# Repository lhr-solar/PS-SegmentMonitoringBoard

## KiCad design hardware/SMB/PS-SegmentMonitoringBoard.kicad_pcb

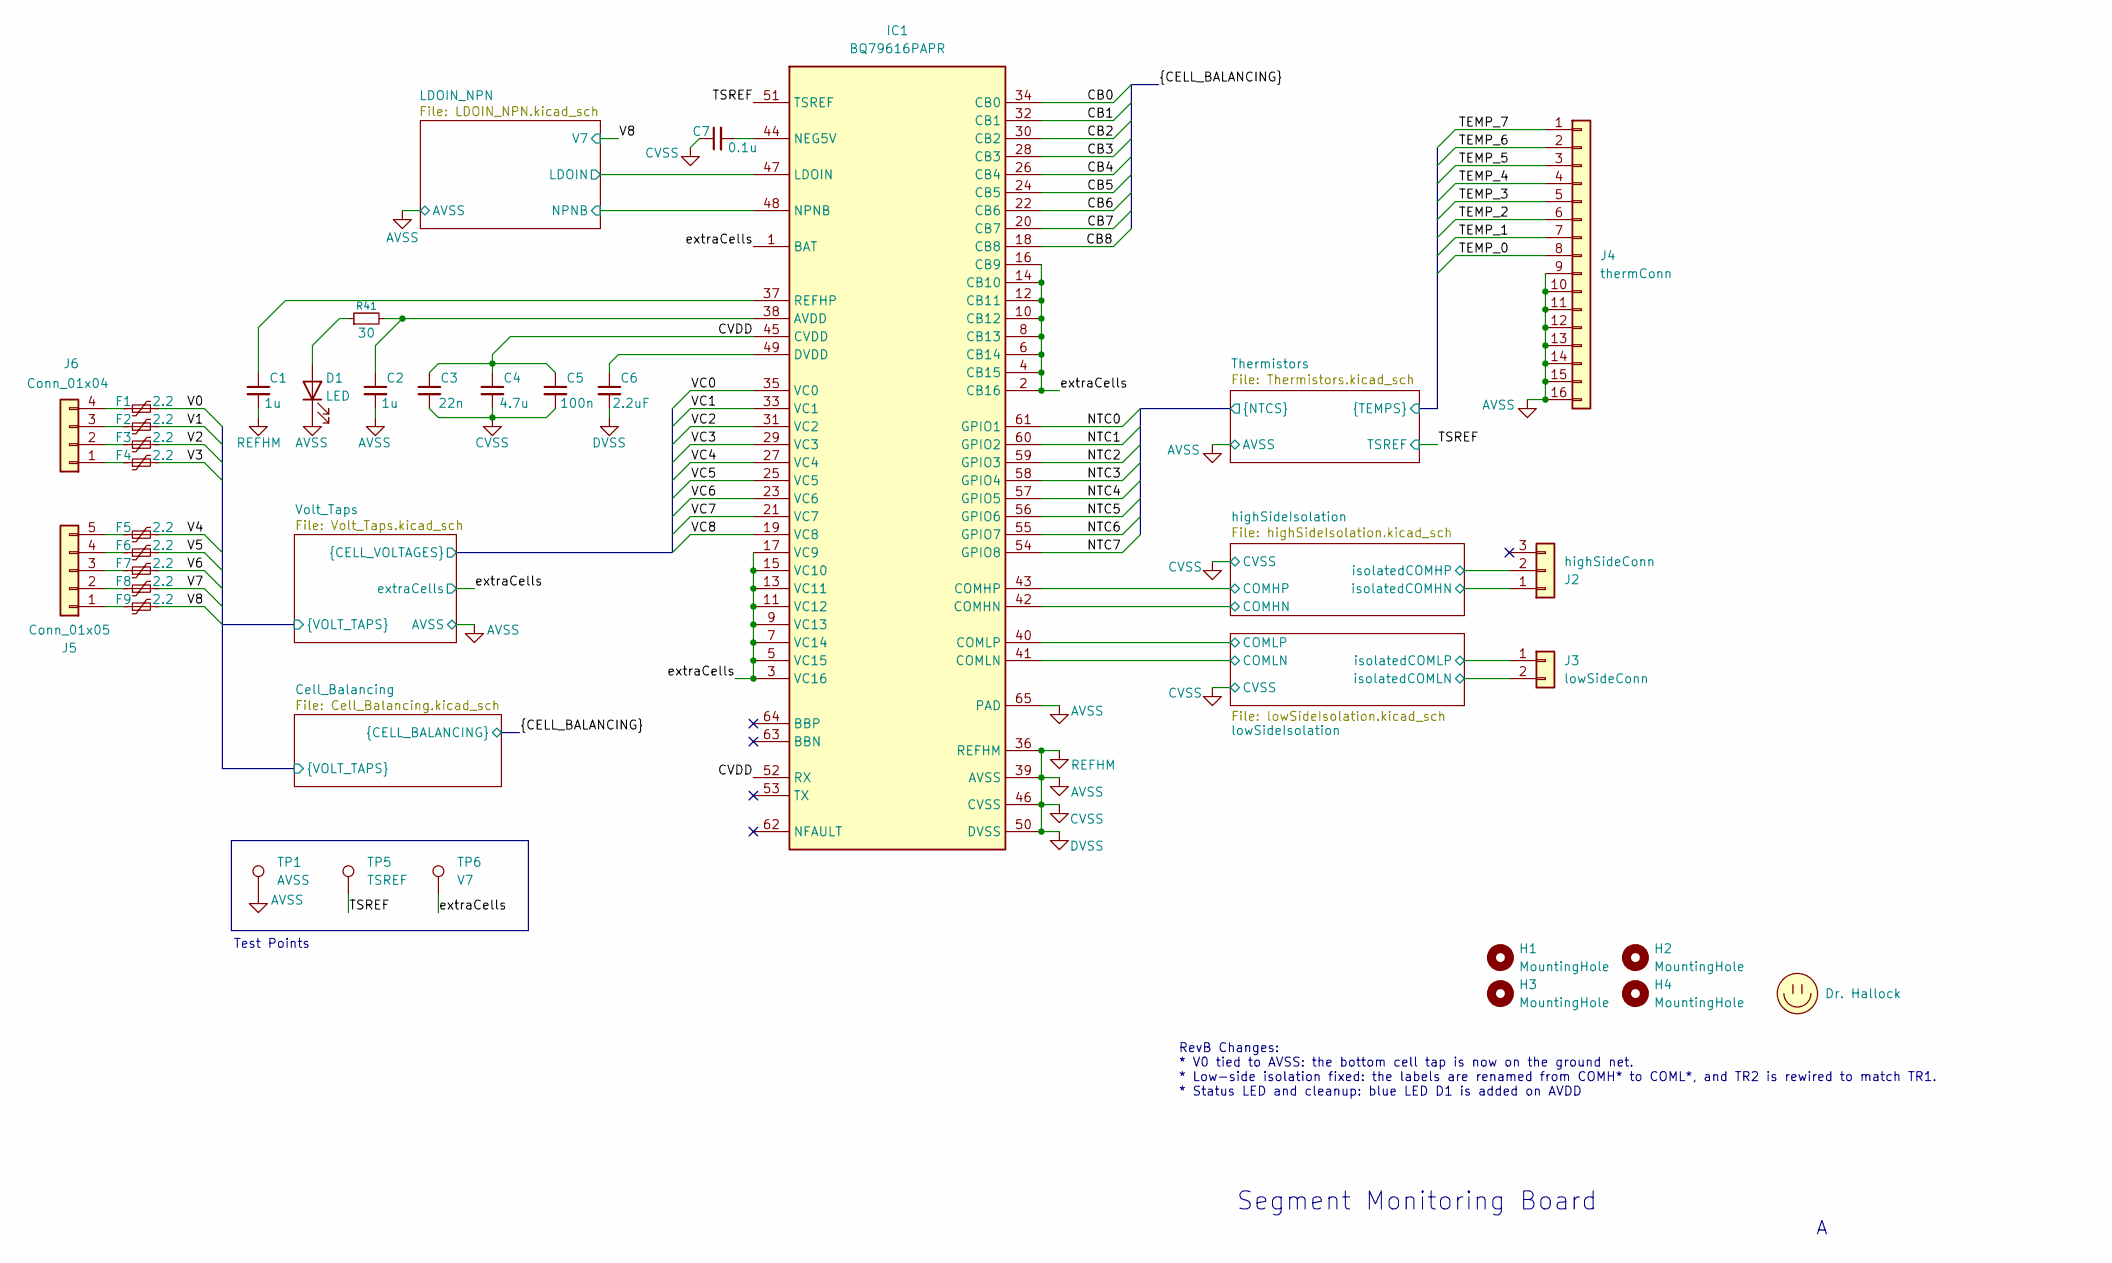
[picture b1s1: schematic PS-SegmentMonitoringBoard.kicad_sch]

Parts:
C1, C2: 1u; C_0603_1608Metric_Pad1.08x0.95mm_HandSolder
C3: 22n; C_0603_1608Metric_Pad1.08x0.95mm_HandSolder
C4: 4.7u; C_0805_2012Metric_Pad1.18x1.45mm_HandSolder
C5: 100n; C_0603_1608Metric_Pad1.08x0.95mm_HandSolder
C6: 2.2uF; C_0603_1608Metric_Pad1.08x0.95mm_HandSolder
C7: 0.1u; C_0603_1608Metric_Pad1.08x0.95mm_HandSolder
D1: LED; LED_0603_1608Metric; LCSC P/N C125103
F1, F2, F3, F4, F5, F6, F7, F8, F9: 2.2; FUSC7451X115N
H1, H2, H3, H4: MountingHole; MountingHole_3.2mm_M3
IC1: BQ79616PAPR; QFP50P1200X1200X120-65N
J2: highSideConn; Molex_Nano-Fit_105313-xx03_1x03_P2.50mm_Horizontal
J3: lowSideConn; Molex_Nano-Fit_105313-xx02_1x02_P2.50mm_Horizontal
J4: thermConn; 1053141116
J5: Conn_01x05; Molex_Nano-Fit_105313-xx05_1x05_P2.50mm_Horizontal
J6: Conn_01x04; Molex_Nano-Fit_105313-xx04_1x04_P2.50mm_Horizontal
LOGO1: Dr. Hallock; LHRs_LOGO
R41: 30; R_0603_1608Metric_Pad0.98x0.95mm_HandSolder
TP1: AVSS; TestPoint_Plated_Hole_D2.0mm
TP5: TSREF; TestPoint_Plated_Hole_D2.0mm
TP6: V7; TestPoint_Plated_Hole_D2.0mm

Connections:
/CB1: IC1.32 (CB1); also elsewhere on the board
/CB2: IC1.30 (CB2); also elsewhere on the board
/CB3: IC1.28 (CB3); also elsewhere on the board
/CB4: IC1.26 (CB4); also elsewhere on the board
/CB5: IC1.24 (CB5); also elsewhere on the board
/CB6: IC1.22 (CB6); also elsewhere on the board
/CVDD: C3.1, C4.1, C5.1, IC1.45 (CVDD), IC1.52 (RX)
/Cell_Balancing/V0: F1.2; also elsewhere on the board
/Cell_Balancing/V1: F2.2; also elsewhere on the board
/Cell_Balancing/V2: F3.2; also elsewhere on the board
/Cell_Balancing/V3: F4.2; also elsewhere on the board
/Cell_Balancing/V4: F5.2; also elsewhere on the board
/Cell_Balancing/V5: F6.2; also elsewhere on the board
/Cell_Balancing/V6: F7.2; also elsewhere on the board
/Cell_Balancing/V7: F8.2; also elsewhere on the board
/Cell_Balancing/V8: F9.2; also elsewhere on the board
/LDOIN_NPN/LDOIN: IC1.47 (LDOIN); also elsewhere on the board
/LDOIN_NPN/NPNB: IC1.48 (NPNB); also elsewhere on the board
/TSREF: IC1.51 (TSREF), TP5.1 (1_1); also elsewhere on the board
/Thermistors/NTC0: IC1.61 (GPIO1); also elsewhere on the board
/Thermistors/NTC1: IC1.60 (GPIO2); also elsewhere on the board
/Thermistors/NTC2: IC1.59 (GPIO3); also elsewhere on the board
/Thermistors/NTC3: IC1.58 (GPIO4); also elsewhere on the board
/Thermistors/NTC4: IC1.57 (GPIO5); also elsewhere on the board
/Thermistors/NTC5: IC1.56 (GPIO6); also elsewhere on the board
/Thermistors/NTC6: IC1.55 (GPIO7); also elsewhere on the board
/Thermistors/NTC7: IC1.54 (GPIO8); also elsewhere on the board
/Thermistors/TEMP_0: J4.8; also elsewhere on the board
/Thermistors/TEMP_1: J4.7; also elsewhere on the board
/Thermistors/TEMP_2: J4.6; also elsewhere on the board
/Thermistors/TEMP_3: J4.5; also elsewhere on the board
/Thermistors/TEMP_4: J4.4; also elsewhere on the board
/Thermistors/TEMP_5: J4.3; also elsewhere on the board
/Thermistors/TEMP_6: J4.2; also elsewhere on the board
/Thermistors/TEMP_7: J4.1; also elsewhere on the board
/Volt_Taps/VC0: IC1.35 (VC0); also elsewhere on the board
/Volt_Taps/VC1: IC1.33 (VC1); also elsewhere on the board
/Volt_Taps/VC2: IC1.31 (VC2); also elsewhere on the board
/Volt_Taps/VC3: IC1.29 (VC3); also elsewhere on the board
/Volt_Taps/VC4: IC1.27 (VC4); also elsewhere on the board
/Volt_Taps/VC5: IC1.25 (VC5); also elsewhere on the board
/Volt_Taps/VC6: IC1.23 (VC6); also elsewhere on the board
/Volt_Taps/VC7: IC1.21 (VC7); also elsewhere on the board
/Volt_Taps/VC8: IC1.19 (VC8); also elsewhere on the board
/extraCells: IC1.1 (BAT), IC1.2 (CB16), IC1.3 (VC16), IC1.4 (CB15), IC1.5 (VC15), IC1.6 (CB14), IC1.7 (VC14), IC1.8 (CB13), IC1.9 (VC13), IC1.10 (CB12), IC1.11 (VC12), IC1.12 (CB11), IC1.13 (VC11), IC1.14 (CB10), IC1.15 (VC10), IC1.16 (CB9), IC1.17 (VC9), TP6.1 (1_1); also elsewhere on the board
/highSideIsolation/COMHN: IC1.42 (COMHN); also elsewhere on the board
/highSideIsolation/COMHP: IC1.43 (COMHP); also elsewhere on the board
/highSideIsolation/isolatedCOMHN: J2.1; also elsewhere on the board
/highSideIsolation/isolatedCOMHP: J2.2; also elsewhere on the board
/lowSideIsolation/COMLN: IC1.41 (COMLN); also elsewhere on the board
/lowSideIsolation/COMLP: IC1.40 (COMLP); also elsewhere on the board
/lowSideIsolation/isolatedCOMLN: J3.2; also elsewhere on the board
/lowSideIsolation/isolatedCOMLP: J3.1; also elsewhere on the board
unnamed: D1.2 (A), R41.1
unnamed: C2.1, IC1.38 (AVDD), R41.2
unnamed: C6.1, IC1.49 (DVDD)
unnamed: C7.2, IC1.44 (NEG5V)
unnamed: C1.1, IC1.37 (REFHP)
unnamed: F9.1, J5.1
unnamed: F8.1, J5.2
unnamed: F7.1, J5.3
unnamed: F6.1, J5.4
unnamed: F5.1, J5.5
unnamed: F4.1, J6.1
unnamed: F3.1, J6.2
unnamed: F2.1, J6.3
unnamed: F1.1, J6.4

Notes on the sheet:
Segment Monitoring Board
Test Points
RevB Changes: * V0 tied to AVSS: the bottom cell tap is now on the ground net. * Low-side isolation fixed: the labels are renamed from COMH* to COML*, and TR2 is rewired to match TR1. * Status LED and cleanup: blue LED D1 is added on AVDD

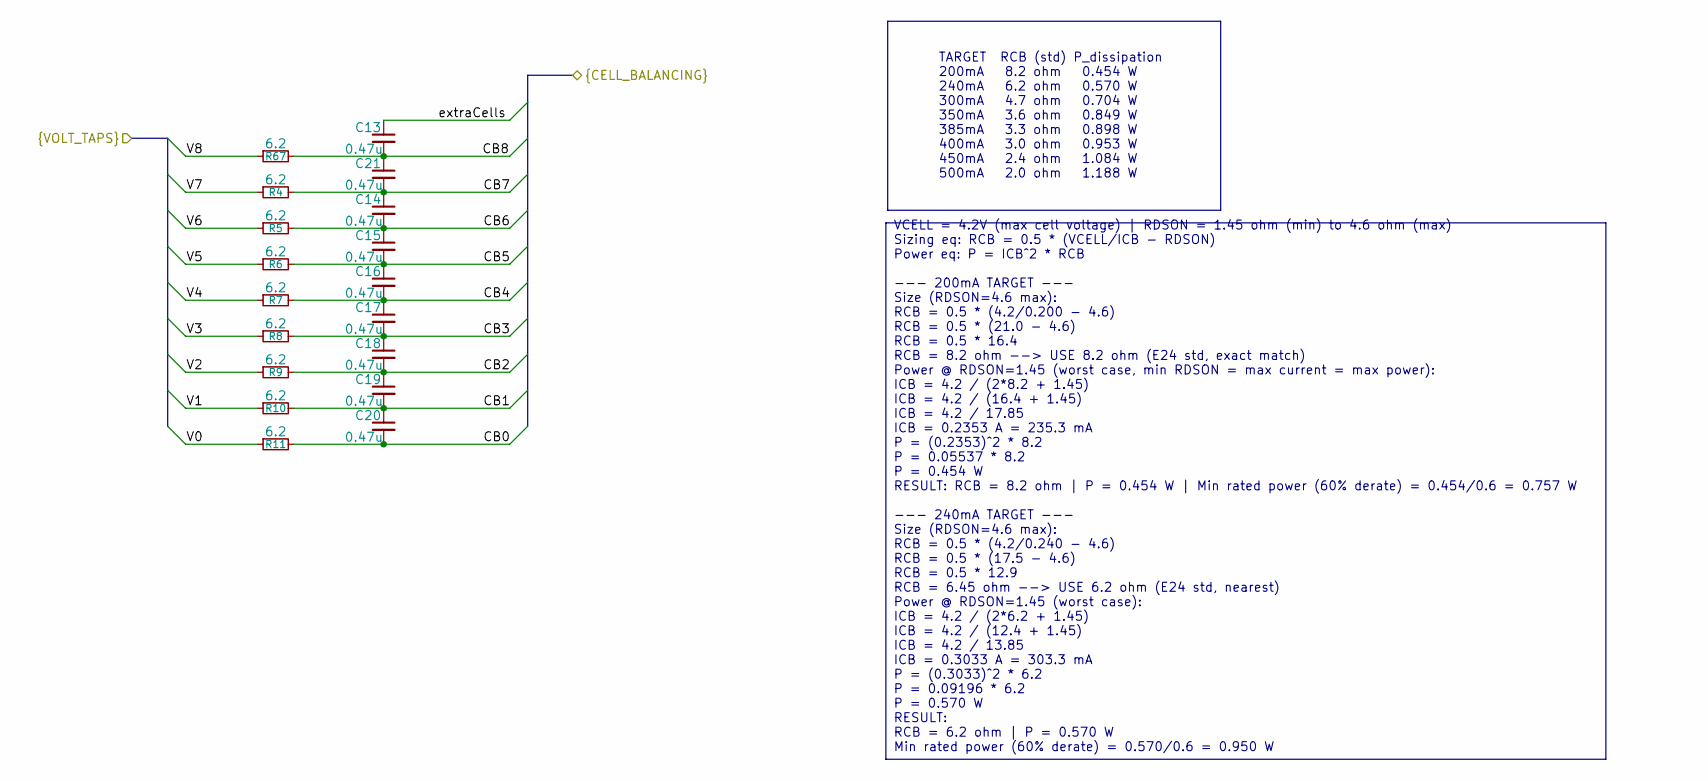
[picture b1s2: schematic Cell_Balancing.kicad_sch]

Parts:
C13, C14, C15, C16, C17, C18, C19, C20, C21: 0.47u; C_0603_1608Metric_Pad1.08x0.95mm_HandSolder
R4, R5, R6, R7, R8, R9, R10, R11, R67: 6.2; R_2512_6332Metric_Pad1.40x3.35mm_HandSolder

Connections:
/CB1: C19.2, C20.1, R10.2; also elsewhere on the board
/CB2: C18.2, C19.1, R9.2; also elsewhere on the board
/CB3: C17.2, C18.1, R8.2; also elsewhere on the board
/CB4: C16.2, C17.1, R7.2; also elsewhere on the board
/CB5: C15.2, C16.1, R6.2; also elsewhere on the board
/CB6: C14.2, C15.1, R5.2; also elsewhere on the board
/Cell_Balancing/V0: R11.1; also elsewhere on the board
/Cell_Balancing/V1: R10.1; also elsewhere on the board
/Cell_Balancing/V2: R9.1; also elsewhere on the board
/Cell_Balancing/V3: R8.1; also elsewhere on the board
/Cell_Balancing/V4: R7.1; also elsewhere on the board
/Cell_Balancing/V5: R6.1; also elsewhere on the board
/Cell_Balancing/V6: R5.1; also elsewhere on the board
/Cell_Balancing/V7: R4.1; also elsewhere on the board
/Cell_Balancing/V8: R67.1; also elsewhere on the board
/extraCells: C13.1; also elsewhere on the board

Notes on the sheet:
VCELL = 4.2V (max cell voltage) | RDSON = 1.45 ohm (min) to 4.6 ohm (max) Sizing eq: RCB = 0.5 * (VCELL/ICB - RDSON) Power eq: P = ICB^2 * RCB --- 200mA TARGET --- Size (RDSON=4.6 max): RCB = 0.5 * (4.2/0.200 - 4.6) RCB = 0.5 * (21.0 - 4.6) RCB = 0.5 * 16.4 RCB = 8.2 ohm --> USE 8.2 ohm (E24 std, e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
TARGET RCB (std) P_dissipation 200mA 8.2 ohm 0.454 W 240mA 6.2 ohm 0.570 W 300mA 4.7 ohm 0.704 W 350mA 3.6 ohm 0.849 W 385mA 3.3 ohm 0.898 W 400mA 3.0 ohm 0.953 W 450mA 2.4 ohm 1.084 W 500mA 2.0 ohm 1.188 W

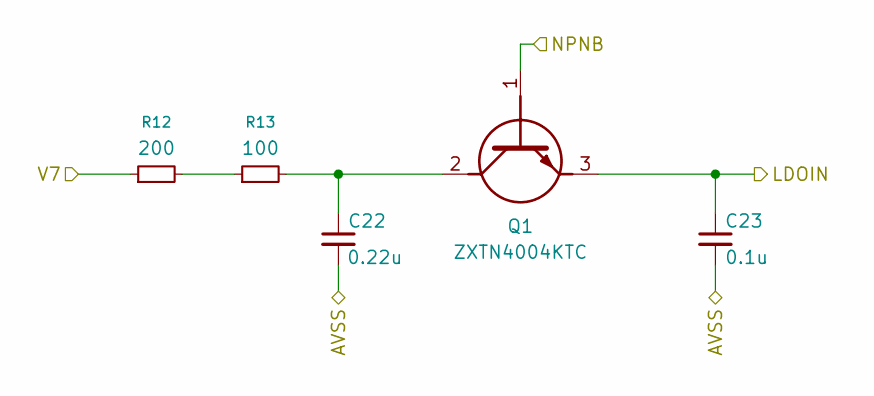
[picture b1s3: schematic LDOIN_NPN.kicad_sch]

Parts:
C22: 0.22u; C_0603_1608Metric_Pad1.08x0.95mm_HandSolder
C23: 0.1u; C_0603_1608Metric_Pad1.08x0.95mm_HandSolder
Q1: ZXTN4004KTC
R12: 200; R_0603_1608Metric_Pad0.98x0.95mm_HandSolder
R13: 100; R_0603_1608Metric_Pad0.98x0.95mm_HandSolder

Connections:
/Cell_Balancing/V8: R12.1; also elsewhere on the board
/LDOIN_NPN/LDOIN: C23.1, Q1.3 (E); also elsewhere on the board
/LDOIN_NPN/NPNB: Q1.1 (B); also elsewhere on the board
unnamed: C22.1, Q1.2 (C), R13.2
unnamed: R12.2, R13.1

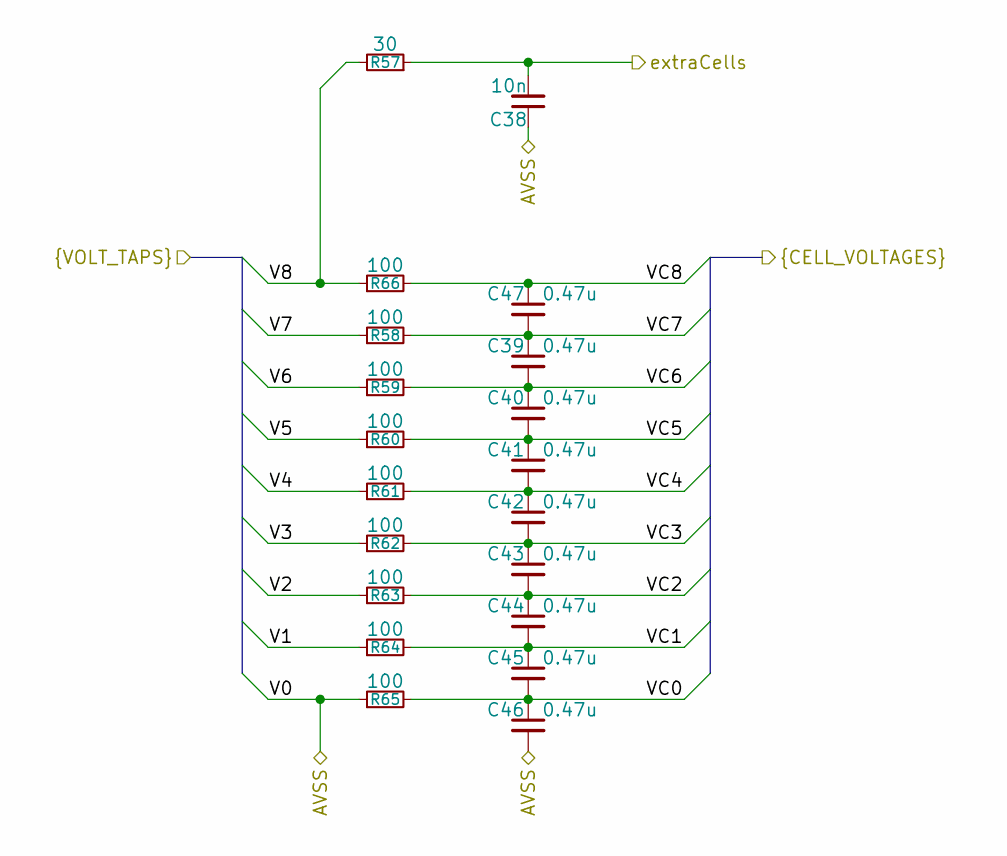
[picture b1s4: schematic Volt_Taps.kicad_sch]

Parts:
C38: 10n; C_0603_1608Metric_Pad1.08x0.95mm_HandSolder
C39, C40, C41, C42, C43, C44, C45, C46, C47: 0.47u; C_0603_1608Metric_Pad1.08x0.95mm_HandSolder
R57: 30; R_0603_1608Metric_Pad0.98x0.95mm_HandSolder
R58, R59, R60, R61, R62, R63, R64, R65, R66: 100; R_0603_1608Metric_Pad0.98x0.95mm_HandSolder

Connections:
/Cell_Balancing/V1: R64.1; also elsewhere on the board
/Cell_Balancing/V2: R63.1; also elsewhere on the board
/Cell_Balancing/V3: R62.1; also elsewhere on the board
/Cell_Balancing/V4: R61.1; also elsewhere on the board
/Cell_Balancing/V5: R60.1; also elsewhere on the board
/Cell_Balancing/V6: R59.1; also elsewhere on the board
/Cell_Balancing/V7: R58.1; also elsewhere on the board
/Cell_Balancing/V8: R57.2, R66.1; also elsewhere on the board
/Volt_Taps/VC0: C45.2, C46.1, R65.2; also elsewhere on the board
/Volt_Taps/VC1: C44.2, C45.1, R64.2; also elsewhere on the board
/Volt_Taps/VC2: C43.2, C44.1, R63.2; also elsewhere on the board
/Volt_Taps/VC3: C42.2, C43.1, R62.2; also elsewhere on the board
/Volt_Taps/VC4: C41.2, C42.1, R61.2; also elsewhere on the board
/Volt_Taps/VC5: C40.2, C41.1, R60.2; also elsewhere on the board
/Volt_Taps/VC6: C39.2, C40.1, R59.2; also elsewhere on the board
/Volt_Taps/VC7: C39.1, C47.2, R58.2; also elsewhere on the board
/Volt_Taps/VC8: C47.1, R66.2; also elsewhere on the board
/extraCells: C38.2, R57.1; also elsewhere on the board

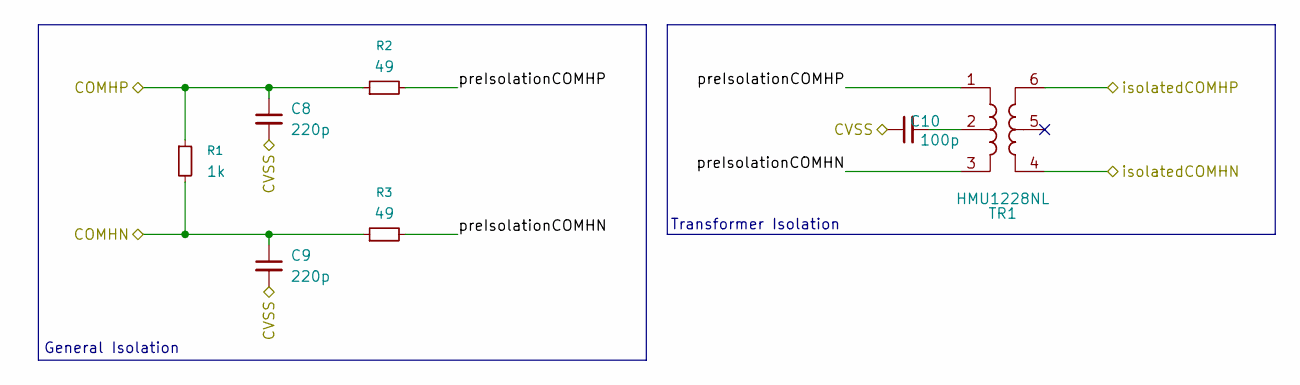
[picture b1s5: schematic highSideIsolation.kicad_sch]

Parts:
C8, C9: 220p; C_0603_1608Metric_Pad1.08x0.95mm_HandSolder
C10: 100p; C_0603_1608Metric_Pad1.08x0.95mm_HandSolder
R1: 1k; R_0603_1608Metric_Pad0.98x0.95mm_HandSolder
R2, R3: 49; R_0603_1608Metric_Pad0.98x0.95mm_HandSolder
TR1: HMU1228NL; SOP254P1270X685-6N

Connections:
/highSideIsolation/COMHN: C9.1, R1.2, R3.1; also elsewhere on the board
/highSideIsolation/COMHP: C8.1, R1.1, R2.1; also elsewhere on the board
/highSideIsolation/isolatedCOMHN: TR1.4; also elsewhere on the board
/highSideIsolation/isolatedCOMHP: TR1.6; also elsewhere on the board
/highSideIsolation/preIsolationCOMHN: R3.2, TR1.3
/highSideIsolation/preIsolationCOMHP: R2.2, TR1.1
unnamed: C10.2, TR1.2

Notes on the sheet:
General Isolation
Transformer Isolation

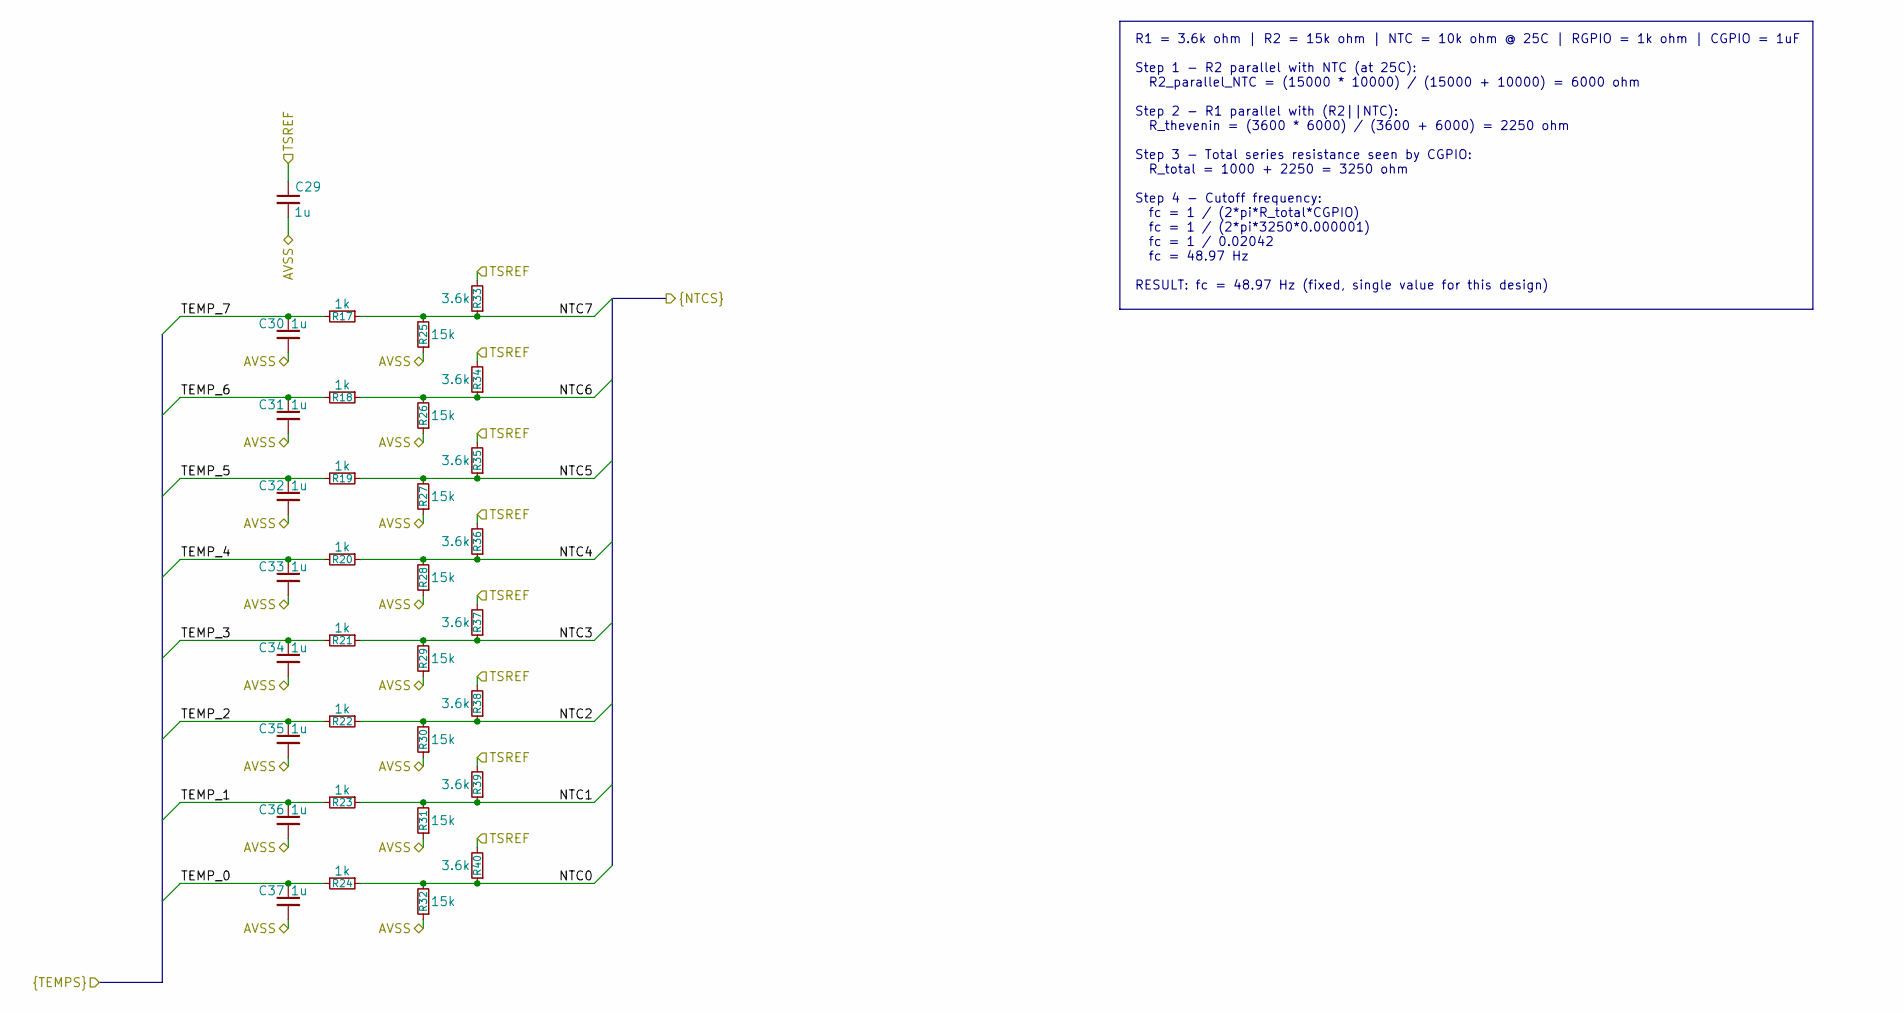
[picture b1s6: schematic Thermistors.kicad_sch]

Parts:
C29, C30, C31, C32, C33, C34, C35, C36, C37: 1u; C_0603_1608Metric_Pad1.08x0.95mm_HandSolder
R17, R18, R19, R20, R21, R22, R23, R24: 1k; R_0603_1608Metric_Pad0.98x0.95mm_HandSolder
R25, R26, R27, R28, R29, R30, R31, R32: 15k; R_0603_1608Metric_Pad0.98x0.95mm_HandSolder
R33, R34, R35, R36, R37, R38, R39, R40: 3.6k; R_0603_1608Metric_Pad0.98x0.95mm_HandSolder

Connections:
/TSREF: C29.1, R33.2, R34.2, R35.2, R36.2, R37.2, R38.2, R39.2, R40.2; also elsewhere on the board
/Thermistors/NTC0: R24.1, R32.2, R40.1; also elsewhere on the board
/Thermistors/NTC1: R23.1, R31.2, R39.1; also elsewhere on the board
/Thermistors/NTC2: R22.1, R30.2, R38.1; also elsewhere on the board
/Thermistors/NTC3: R21.1, R29.2, R37.1; also elsewhere on the board
/Thermistors/NTC4: R20.1, R28.2, R36.1; also elsewhere on the board
/Thermistors/NTC5: R19.1, R27.2, R35.1; also elsewhere on the board
/Thermistors/NTC6: R18.1, R26.2, R34.1; also elsewhere on the board
/Thermistors/NTC7: R17.1, R25.2, R33.1; also elsewhere on the board
/Thermistors/TEMP_0: C37.1, R24.2; also elsewhere on the board
/Thermistors/TEMP_1: C36.1, R23.2; also elsewhere on the board
/Thermistors/TEMP_2: C35.1, R22.2; also elsewhere on the board
/Thermistors/TEMP_3: C34.1, R21.2; also elsewhere on the board
/Thermistors/TEMP_4: C33.1, R20.2; also elsewhere on the board
/Thermistors/TEMP_5: C32.1, R19.2; also elsewhere on the board
/Thermistors/TEMP_6: C31.1, R18.2; also elsewhere on the board
/Thermistors/TEMP_7: C30.1, R17.2; also elsewhere on the board

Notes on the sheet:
R1 = 3.6k ohm | R2 = 15k ohm | NTC = 10k ohm @ 25C | RGPIO = 1k ohm | CGPIO = 1uF Step 1 - R2 parallel with NTC (at 25C): R2_parallel_NTC = (15000 * 10000) / (15000 + 10000) = 6000 ohm Step 2 - R1 parallel with (R2||NTC): R_thevenin = (3600 * 6000) / (3600 + 6000) = 2250 ohm Step 3 - Total series r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

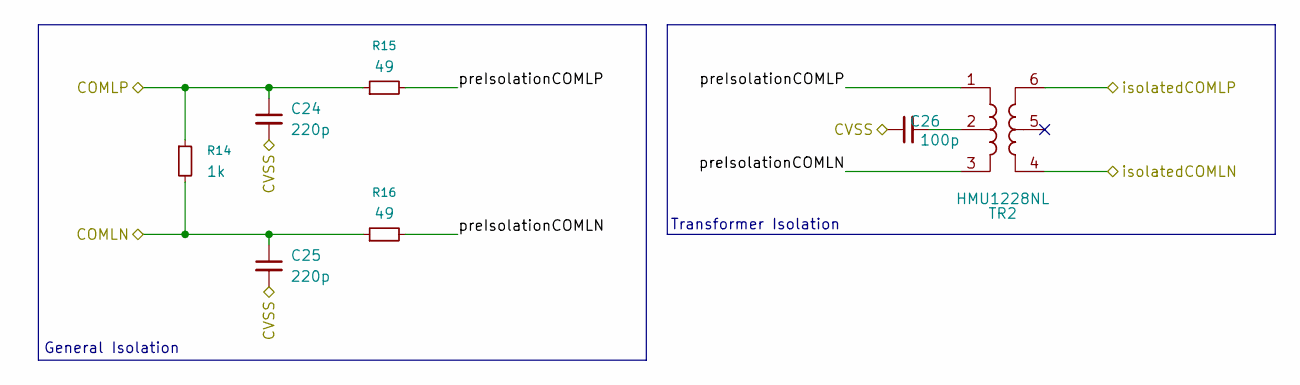
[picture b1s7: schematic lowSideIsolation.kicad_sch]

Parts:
C24, C25: 220p; C_0603_1608Metric_Pad1.08x0.95mm_HandSolder
C26: 100p; C_0603_1608Metric_Pad1.08x0.95mm_HandSolder
R14: 1k; R_0603_1608Metric_Pad0.98x0.95mm_HandSolder
R15, R16: 49; R_0603_1608Metric_Pad0.98x0.95mm_HandSolder
TR2: HMU1228NL; SOP254P1270X685-6N

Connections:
/lowSideIsolation/COMLN: C25.1, R14.2, R16.1; also elsewhere on the board
/lowSideIsolation/COMLP: C24.1, R14.1, R15.1; also elsewhere on the board
/lowSideIsolation/isolatedCOMLN: TR2.4; also elsewhere on the board
/lowSideIsolation/isolatedCOMLP: TR2.6; also elsewhere on the board
/lowSideIsolation/preIsolationCOMLN: R16.2, TR2.3
/lowSideIsolation/preIsolationCOMLP: R15.2, TR2.1
unnamed: C26.2, TR2.2

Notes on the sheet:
Transformer Isolation
General Isolation

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
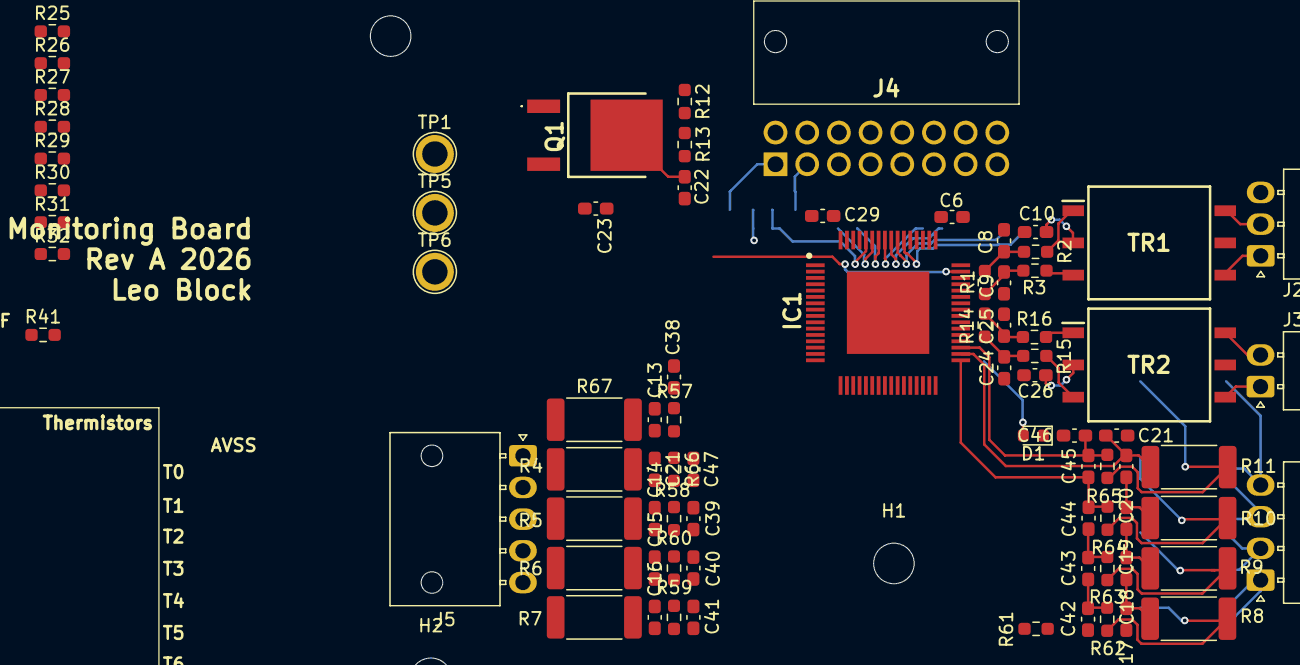
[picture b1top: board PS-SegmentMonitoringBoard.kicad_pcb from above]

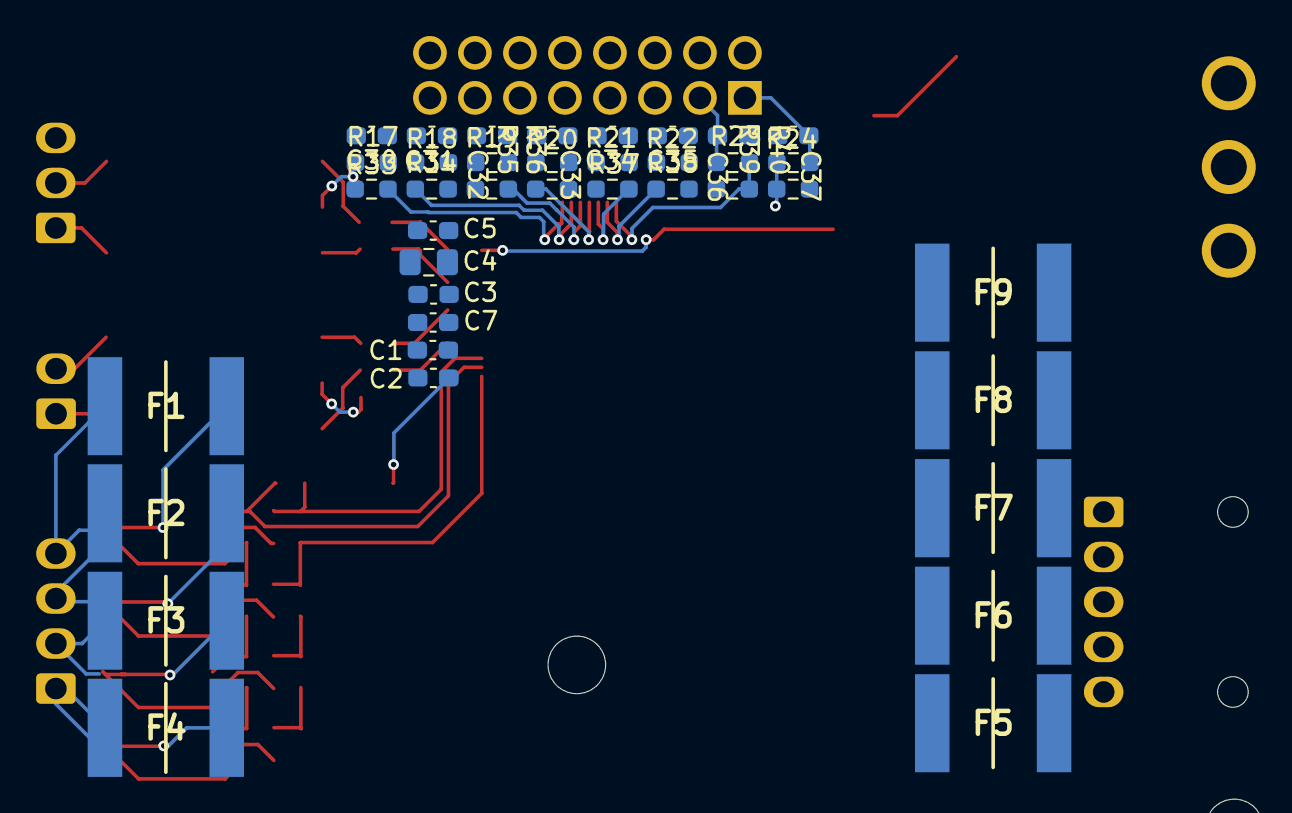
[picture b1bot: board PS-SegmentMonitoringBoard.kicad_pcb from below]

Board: 4 copper layers, 123 parts (39 on the bottom side), 79 nets.

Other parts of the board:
C21#2: 0.47u; C_0603_1608Metric_Pad1.08x0.95mm_HandSolder
